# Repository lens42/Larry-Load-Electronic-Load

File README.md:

This simple electronic load for testing power supply circuits was a popular lab-built piece of test gear at Maxim Integrated Products. It came to be known as the "Larry Load" by the lab rats at Maxim, because the design originated from an applications engineer named Larry Carr. Commercial electronic loads were available from companies like Kikusui, but those were not cheap (while Maxim famously *was* back then) and Larry Loads were unique in their simplicity, wide range, and every-day utility. After retiring from Maxim. I had always intended to build a few of these for home lab use. I finally did just that.

3D files for the case include only the top section. Features are cut into a 3" section of 4"x2" alumimum U-channel. The bottom half is the same as the top, but without the pockets and the mounting holes for MOSFETs.

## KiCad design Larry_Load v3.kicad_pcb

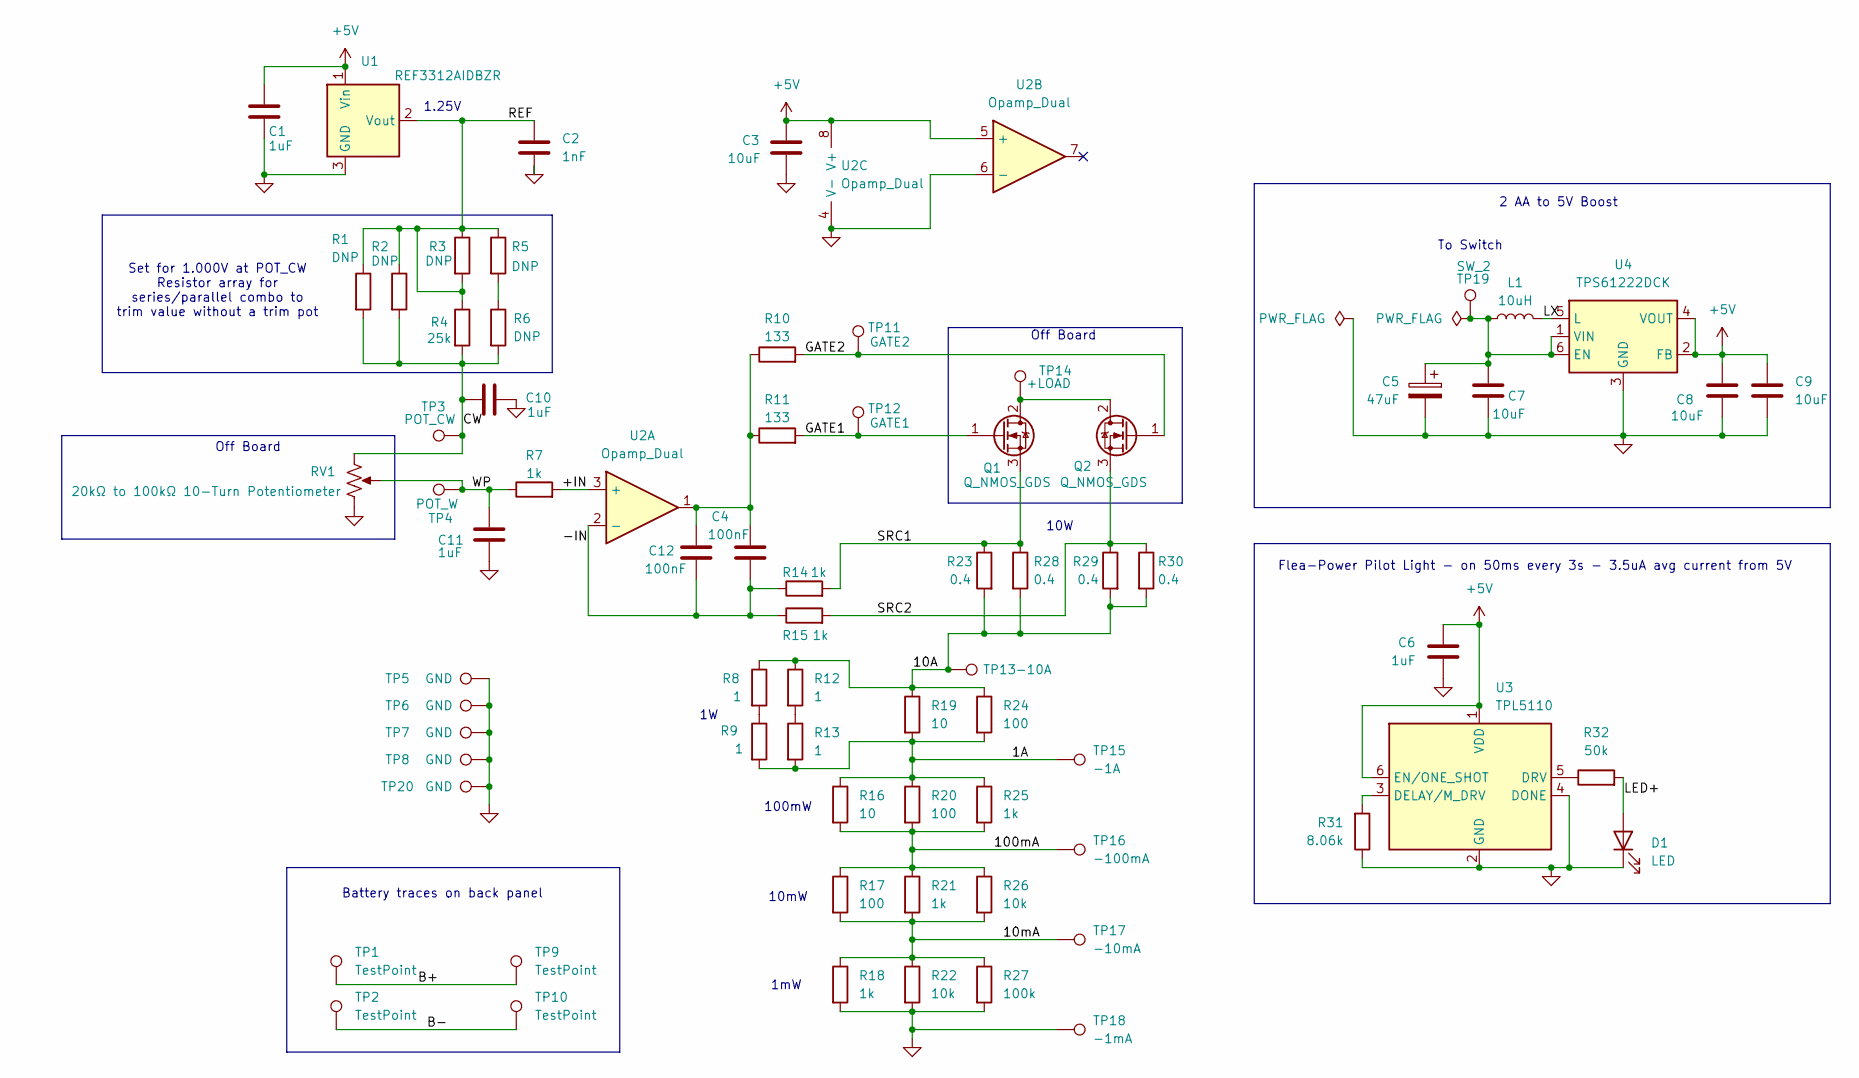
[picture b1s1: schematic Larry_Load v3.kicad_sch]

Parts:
C1, C6, C10, C11: 1uF; C_0805_2012Metric_Pad1.18x1.45mm_HandSolder
C2: 1nF; C_0805_2012Metric_Pad1.18x1.45mm_HandSolder
C3, C7, C8, C9: 10uF; C_1206_3216Metric_Pad1.33x1.80mm_HandSolder
C4, C12: 100nF; C_0805_2012Metric_Pad1.18x1.45mm_HandSolder
C5: 47uF; CP_Elec_6.3x7.7
D1: LED; LED_VLDTG1232R-08_ReverseMount
L1: 10uH; L_Cenker_CKCS5020
Q1, Q2: Q_NMOS_GDS
R1, R2, R3, R5, R6: DNP; R_1206_3216Metric_Pad1.30x1.75mm_HandSolder
R4: 25k; R_1206_3216Metric_Pad1.30x1.75mm_HandSolder
R7, R14, R15, R18, R21, R25: 1k; R_1206_3216Metric_Pad1.30x1.75mm_HandSolder
R8, R9, R12, R13: 1; R_1206_3216Metric_Pad1.30x1.75mm_HandSolder
R10, R11: 133; R_1206_3216Metric_Pad1.30x1.75mm_HandSolder
R16, R19: 10; R_1206_3216Metric_Pad1.30x1.75mm_HandSolder
R17, R20, R24: 100; R_1206_3216Metric_Pad1.30x1.75mm_HandSolder
R22, R26: 10k; R_1206_3216Metric_Pad1.30x1.75mm_HandSolder
R23, R28, R29, R30: 0.4; R_2512_6332Metric_Pad1.40x3.35mm_HandSolder
R27: 100k; R_1206_3216Metric_Pad1.30x1.75mm_HandSolder
R31: 8.06k; R_1206_3216Metric_Pad1.30x1.75mm_HandSolder
R32: 50k; R_1206_3216Metric_Pad1.30x1.75mm_HandSolder
RV1: 20kΩ to 100kΩ 10-Turn Potentiometer
TP1, TP2, TP9, TP10: TestPoint; TestPoint_Pad_4.0x6.0mm
TP3: POT_CW; TestPoint_Pad_4.0x6.0mm
TP4: POT_W; TestPoint_Pad_4.0x6.0mm
TP5, TP6, TP7, TP8, TP20: GND; TestPoint_Pad_4.0x6.0mm
TP11: GATE2; TestPoint_Pad_4.0x6.0mm
TP12: GATE1; TestPoint_Pad_4.0x6.0mm
TP13: -10A; MountingHole_5.3mm_M5_DIN965_Pad_TopBottom
TP14: +LOAD; TestPoint_Pad_4.0x6.0mm
TP15: -1A; MountingHole_5.3mm_M5_DIN965_Pad_TopBottom
TP16: -100mA; MountingHole_5.3mm_M5_DIN965_Pad_TopBottom
TP17: -10mA; MountingHole_5.3mm_M5_DIN965_Pad_TopBottom
TP18: -1mA; MountingHole_5.3mm_M5_DIN965_Pad_TopBottom
TP19: SW_2; TestPoint_Pad_4.0x6.0mm
U1: REF3312AIDBZR; SOT-23
U2: Opamp_Dual; SO-8_3.9x4.9mm_P1.27mm
U3: TPL5110; SOT-23-6
U4: TPS61222DCK; Texas_R-PDSO-G6

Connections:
+5V: C1.1, C3.1, C6.2, C8.1, C9.1, U1.1 (Vin), U2.5 (+), U2.8 (V+), U3.1 (VDD), U3.6 (EN/ONE_SHOT), U4.2 (FB), U4.4 (VOUT)
/1A: R9.2, R13.2, R16.1, R19.2, R20.1, R24.2, R25.1, TP15.1
/10A: R8.1, R12.1, R19.1, R23.2, R24.1, R28.2, R29.2, R30.2, TP13.1
/10mA: R17.2, R18.1, R21.2, R22.1, R26.2, R27.1, TP17.1
/100mA: R16.2, R17.1, R20.2, R21.1, R25.2, R26.1, TP16.1
/+IN: R7.2, U2.3 (+)
/-IN: C4.2, C12.2, R14.1, R15.1, U2.2 (-)
/B+: TP1.1, TP9.1
/B-: TP2.1, TP10.1
/CW: C10.1, R1.2, R2.2, R4.2, R6.2, RV1.1, TP3.1
/GATE1: Q1.1 (G), R11.2, TP12.1
/GATE2: Q2.1 (G), R10.2, TP11.1
/LED+: D1.2 (A), R32.2
/LX: L1.2, U4.5 (L)
/REF: C2.1, R1.1, R2.1, R3.1, R3.2, R4.1, R5.1, U1.2 (Vout)
/SRC1: Q1.3 (S), R14.2, R23.1, R28.1
/SRC2: Q2.3 (S), R15.2, R29.1, R30.1
/WP: C11.1, R7.1, RV1.2, TP4.1
GND: C1.2, C2.2, C3.2, C5.2, C6.1, C7.2, C8.2, C9.2, C10.2, C11.2, D1.1 (K), R18.2, R22.2, R27.2, R31.1, RV1.3, TP5.1, TP6.1, TP7.1, TP8.1, TP18.1, TP20.1, U1.3 (GND), U2.4 (V-), U2.6 (-), U3.2 (GND), U3.4 (DONE), U4.3 (GND)
unnamed: C4.1, C12.1, R10.1, R11.1, U2.1
unnamed: Q1.2 (D), Q2.2 (D), TP14.1
unnamed: R5.2, R6.1
unnamed: R8.2, R9.1
unnamed: R12.2, R13.1
unnamed: R31.2, U3.3 (DELAY/M_DRV)
unnamed: R32.1, U3.5 (DRV)
unnamed: C5.1, C7.1, L1.1, TP19.1, U4.1 (VIN), U4.6 (EN)

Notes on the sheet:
Off Board
1.25V
10mW
10W
To Switch
Flea-Power Pilot Light - on 50ms every 3s - 3.5uA avg current from 5V
1mW
100mW
Battery traces on back panel
2 AA to 5V Boost
Set for 1.000V at POT_CW Resistor array for series/parallel combo to trim value without a trim pot

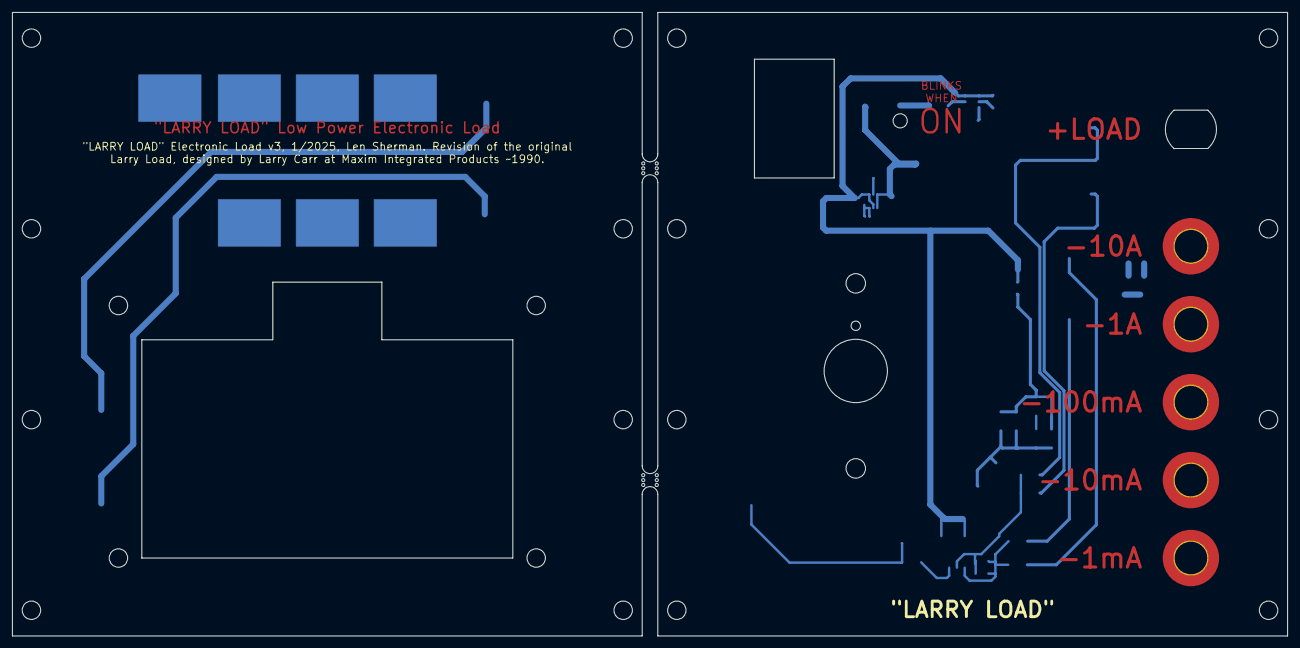
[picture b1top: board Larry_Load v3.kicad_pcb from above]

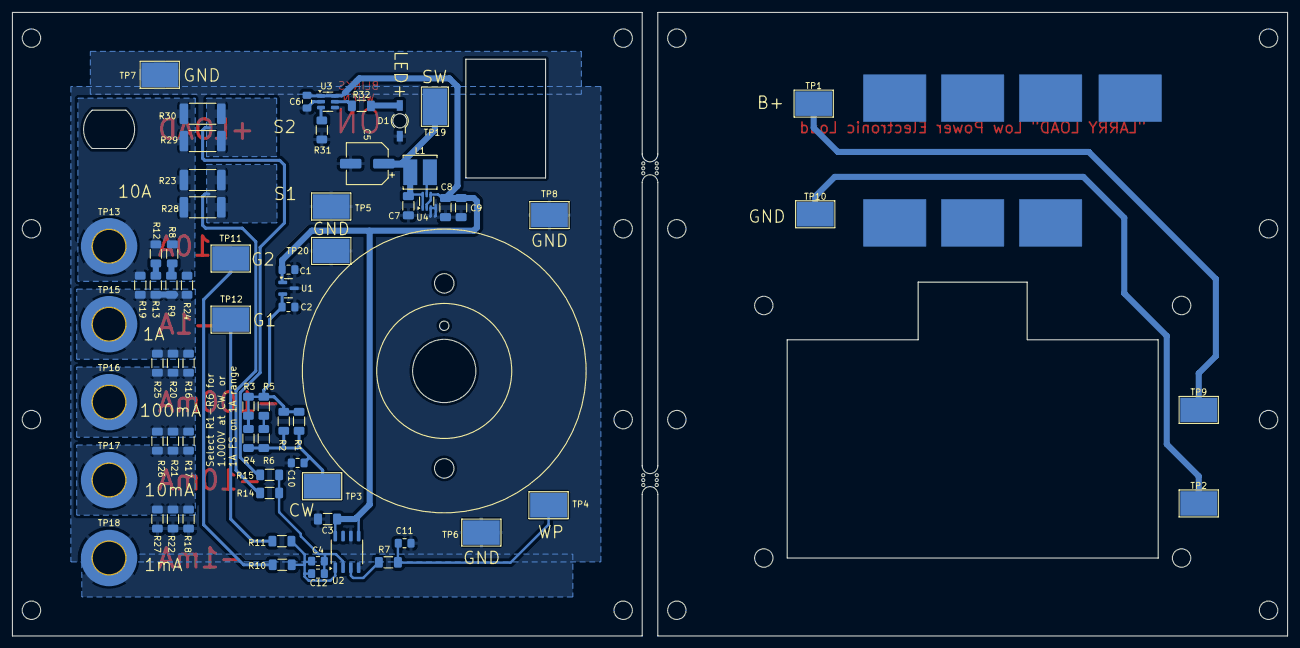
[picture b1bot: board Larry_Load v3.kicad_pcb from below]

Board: 2 copper layers, 207.7 x 101.5 mm, 71 parts (69 on the bottom side), 26 nets.

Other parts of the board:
mouse-bite-2.54mm-slot, mouse-bite-2.54mm-slot#2: VAL**; mouse-bite-2.54mm-slot

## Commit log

2025-02-18 Add files via upload
    Adding 3D files for the case top. Bottom is same file without some of the features.
2025-03-10 Add files via upload
    Fixed incorrect values for LED blinker
2025-03-10 Add files via upload
    Fixed incorrect values for R31, R32
